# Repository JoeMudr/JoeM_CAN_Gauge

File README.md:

# JoeM CAN Gauge
Configurable Gauge receiving data via CAN bus.

* ATMEGA328P 
* MCP2515 
* MCP2551

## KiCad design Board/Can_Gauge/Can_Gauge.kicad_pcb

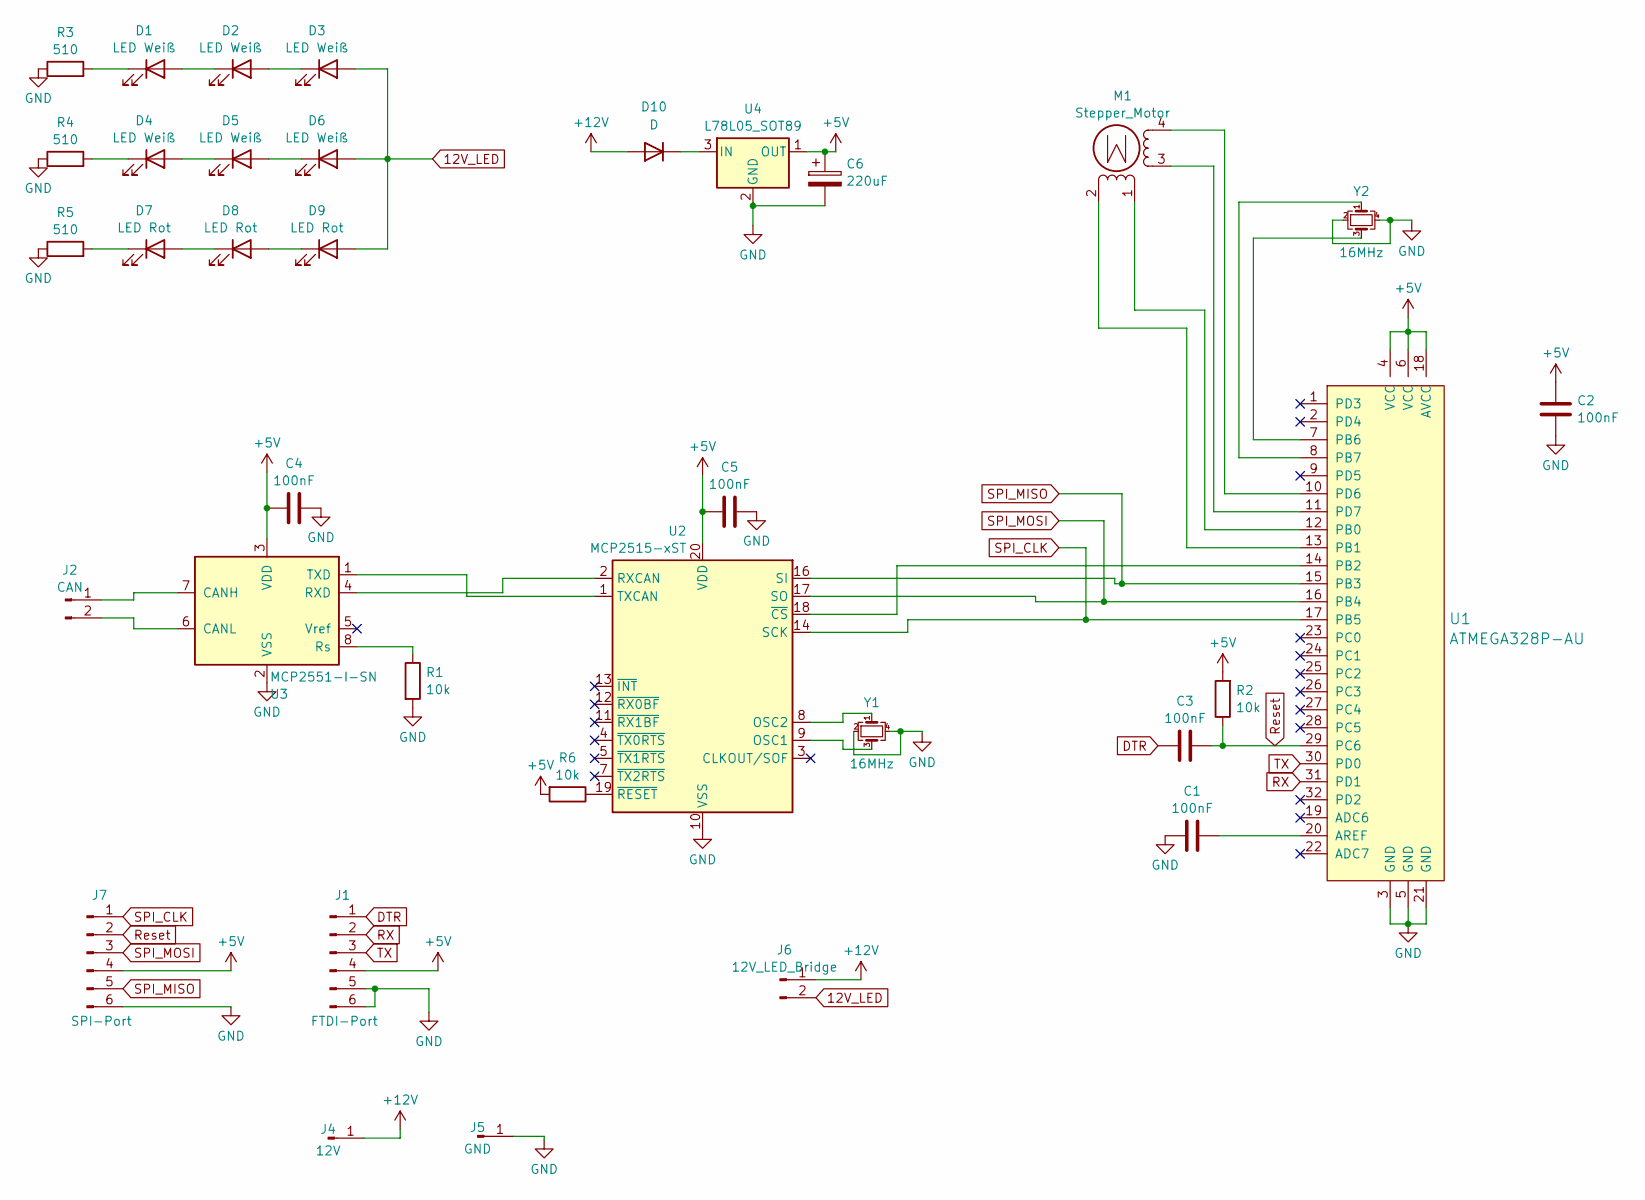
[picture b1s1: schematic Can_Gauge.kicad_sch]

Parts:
C1, C2, C3, C4, C5: 100nF; C_0603_1608Metric; LCSC C14663
C6: 220uF; CP_Elec_6.3x7.7; LCSC C4747974
D1, D2, D3, D4, D5, D6: LED Weiß; LED_PLCC_2835_Handsoldering; LCSC C516134
D7, D8, D9: LED Rot; LED_PLCC_2835_Handsoldering; LCSC C2843869
D10: D; D_SOD-123F; LCSC C64898
J1: FTDI-Port; PinHeader_1x06_P2.54mm_Vertical
J2: CAN; PinHeader_1x02_P2.54mm_Vertical
J4: 12V; PinHeader_1x01_P2.54mm_Vertical
J5: GND; PinHeader_1x01_P2.54mm_Vertical
J6: 12V_LED_Bridge; PinHeader_1x02_P2.54mm_Vertical
J7: SPI-Port; PinHeader_2x03_P1.27mm_Vertical
M1: Stepper_Motor; StepperMotor
R1, R2, R6: 10k; R_0603_1608Metric; LCSC C25804
R3, R4, R5: 510; R_0805_2012Metric; LCSC C17734
U1: ATMEGA328P-AU; TQFP-32_7x7mm; MPN ATMEGA328P-AU; Digi-Key_PN ATMEGA328P-AU-ND
U2: MCP2515-xST; TSSOP-20_4.4x6.5mm_P0.65mm
U3: MCP2551-I-SN; SOIC-8_3.9x4.9mm_P1.27mm; LCSC C49558
U4: L78L05_SOT89; SOT-89-3; LCSC C347258
Y1, Y2: 16MHz; Crystal_SMD_2016-4Pin_2.0x1.6mm; LCSC C2965579

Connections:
12V_LED: D3.2 (A), D6.2 (A), D9.2 (A), J6.2
+5V: C2.2, C4.2, C5.2, C6.1, J1.4, J7.4, R2.2, R6.2, U1.4 (VCC), U1.6 (VCC), U1.18 (AVCC), U2.20 (VDD), U3.3 (VDD), U4.1 (OUT)
+12V: D10.2 (A), J4.1, J6.1
DTR: C3.1, J1.1
GND: C1.1, C2.1, C4.1, C5.1, C6.2, J1.5, J1.6, J5.1, J7.6, R1.2, R3.1, R4.1, R5.1, U1.3 (GND), U1.5 (GND), U1.21 (GND), U2.10 (VSS), U3.2 (VSS), U4.2 (GND), Y1.2, Y1.4, Y2.2, Y2.4
unnamed: D1.2 (A), D2.1 (K)
unnamed: D1.1 (K), R3.2
unnamed: D2.2 (A), D3.1 (K)
unnamed: D4.2 (A), D5.1 (K)
unnamed: D4.1 (K), R4.2
unnamed: D5.2 (A), D6.1 (K)
unnamed: D7.2 (A), D8.1 (K)
unnamed: D7.1 (K), R5.2
unnamed: D8.2 (A), D9.1 (K)
unnamed: D10.1 (K), U4.3 (IN)
unnamed: J2.1, U3.7 (CANH)
unnamed: J2.2, U3.6 (CANL)
unnamed: M1.2 (-), U1.13 (PB1)
unnamed: C1.2, U1.20 (AREF)
unnamed: M1.1, U1.12 (PB0)
unnamed: U1.14 (PB2), U2.18 (~CS)
unnamed: U1.7 (PB6), Y2.3
unnamed: U1.8 (PB7), Y2.1
unnamed: M1.4, U1.10 (PD6)
unnamed: M1.3, U1.11 (PD7)
unnamed: U2.9 (OSC1), Y1.3
unnamed: U2.8 (OSC2), Y1.1
unnamed: U2.2 (RXCAN), U3.4 (RXD)
unnamed: U2.1 (TXCAN), U3.1 (TXD)
unnamed: R6.1, U2.19 (~RESET)
unnamed: R1.1, U3.8 (Rs)
RX: J1.2, U1.31 (PD1)
Reset: C3.2, J7.2, R2.1, U1.29 (PC6)
SPI_CLK: J7.1, U1.17 (PB5), U2.14 (SCK)
SPI_MISO: J7.5, U1.15 (PB3), U2.16 (SI)
SPI_MOSI: J7.3, U1.16 (PB4), U2.17 (SO)
TX: J1.3, U1.30 (PD0)

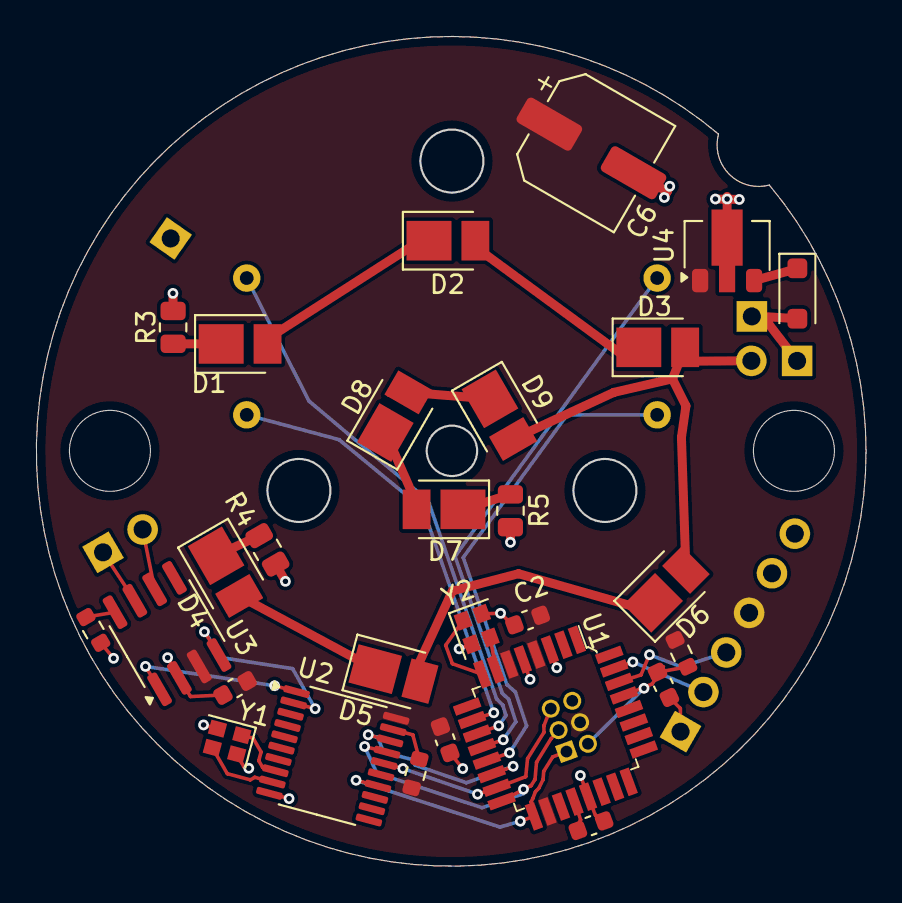
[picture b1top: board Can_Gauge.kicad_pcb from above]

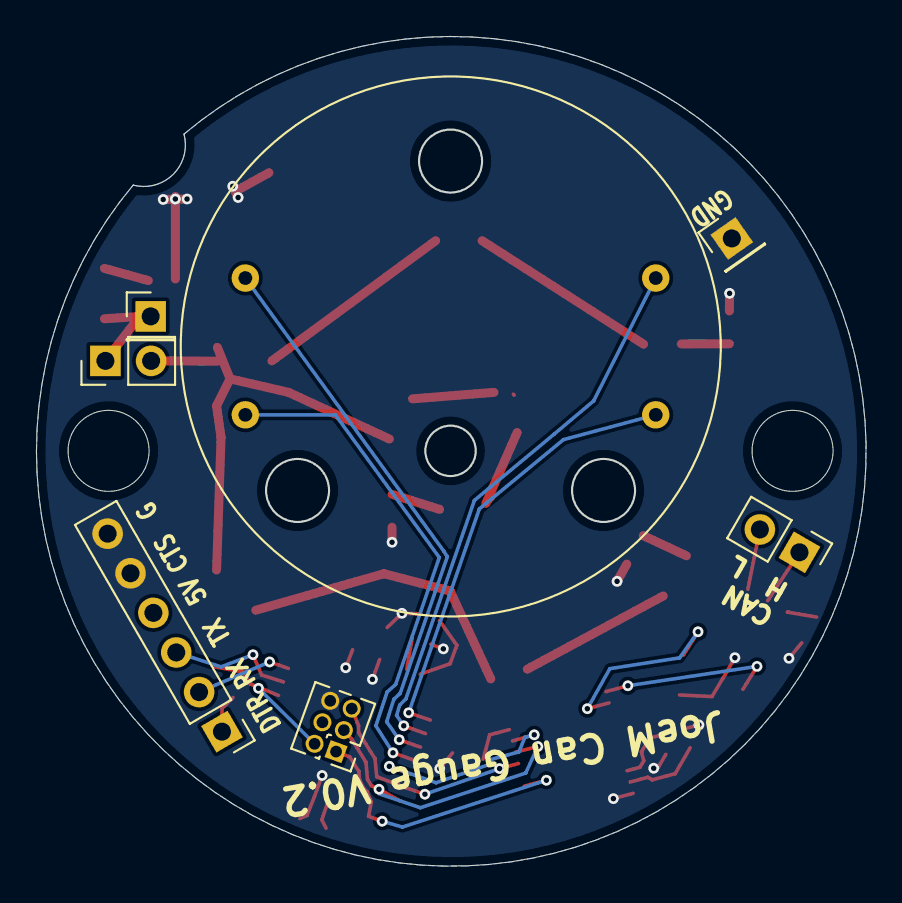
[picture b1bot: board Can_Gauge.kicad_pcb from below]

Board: 2 copper layers, 46.0 x 46.0 mm, 35 parts (7 on the bottom side), 37 nets.

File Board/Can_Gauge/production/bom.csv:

Designator,Footprint,Quantity,Value,LCSC Part #
"C1, C2, C3, C4, C5",0603,5,100nF,C14663
C6,CP_Elec_6.3x7.7,1,220uF,C4747974
"D1, D2, D3, D4, D5, D6",LED_PLCC_2835_Handsoldering,6,LED Weiß,C516134
D10,D_SOD-123F,1,D,C64898
"D7, D8, D9",LED_PLCC_2835_Handsoldering,3,LED Rot,C2843869
J1,PinHeader_1x06_P2.54mm_Vertical,1,FTDI-Port,
J2,PinHeader_1x02_P2.54mm_Vertical,1,CAN,
J4,PinHeader_1x01_P2.54mm_Vertical,1,12V,
J5,PinHeader_1x01_P2.54mm_Vertical,1,GND,
J6,PinHeader_1x02_P2.54mm_Vertical,1,12V_LED_Bridge,
J7,PinHeader_2x03_P1.27mm_Vertical,1,SPI-Port,
M1,StepperMotor,1,Stepper_Motor,
"R1, R2, R6",0603,3,10k,C25804
"R3, R4, R5",0805,3,510,C17734
U1,TQFP-32_7x7mm,1,ATMEGA328P-AU,ATMEGA328P-AU
U2,TSSOP-20_4.4x6.5mm_P0.65mm,1,MCP2515-xST,
U3,SOIC-8_3.9x4.9mm_P1.27mm,1,MCP2551-I-SN,C49558
U4,SOT-89-3,1,L78L05_SOT89,C347258
"Y1, Y2",Crystal_SMD_2016-4Pin_2.0x1.6mm,2,16MHz,C2965579

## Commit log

2024-05-24 Init
2024-05-24 Add menu option for Boud rate; modify MCP2515-Lib.
2024-05-24 Readme Update
2024-05-24 license
2024-06-12 Board adjustments
2024-06-12 Fixes for first prototype
2024-06-12 FW-Version & Board Backup removed
2024-06-20 Gauge faces; Init move; restructure Board
2024-06-30 Board: Add protection Diode
2024-06-30 Add configurable Angles; Fix negative values; Change Stepper_Drive to aangle; Reduce stepper speed.
2024-07-03 Fix Stepper_Drive calc
